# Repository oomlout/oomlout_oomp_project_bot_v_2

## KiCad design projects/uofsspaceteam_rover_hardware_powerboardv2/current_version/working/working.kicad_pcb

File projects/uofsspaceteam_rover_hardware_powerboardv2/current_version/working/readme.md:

# rover_hardware
 
## summary 
* id: uofsspaceteam_rover_hardware_powerboardv2
* user: uofsspaceteam
* name: rover_hardware
* board: powerboardv2
* repo: https://github.com/UofSSpaceTeam/rover-hardware
* src_file_repo_kicad_pcb: Projects/Power Distribution/PowerBoardV2/gerber/PowerBoardV2.kicad_pcb
* src_file_repo_kicad_pcb_link: https://github.com/UofSSpaceTeam/rover-hardware/tree/master/Projects/Power Distribution/PowerBoardV2/gerber/PowerBoardV2.kicad_pcb
* src_file_repo_kicad_sch: Projects/Power Distribution/DriveController/DriveControllerPower.kicad_sch
* src_file_repo_kicad_sch_link: https://github.com/UofSSpaceTeam/rover-hardware/tree/master/Projects/Power Distribution/DriveController/DriveControllerPower.kicad_sch
* src_file_repo_brd: Projects/Communication/KiCad_USB/modified_eagle_files/RH025.1.brd
* src_file_repo_brd_link: https://github.com/UofSSpaceTeam/rover-hardware/tree/master/Projects/Communication/KiCad_USB/modified_eagle_files/RH025.1.brd
* src_file_repo_sch: Projects/Power Distribution/PowerBoardV2/PowerBoardV2.sch
* src_file_repo_sch_link: https://github.com/UofSSpaceTeam/rover-hardware/tree/master/Projects/Power Distribution/PowerBoardV2/PowerBoardV2.sch
* full details link: https://github.com/oomlout/oomlout_oomp_project_bot_v_2/tree/main/projects/uofsspaceteam_rover_hardware_powerboardv2/current_version/working

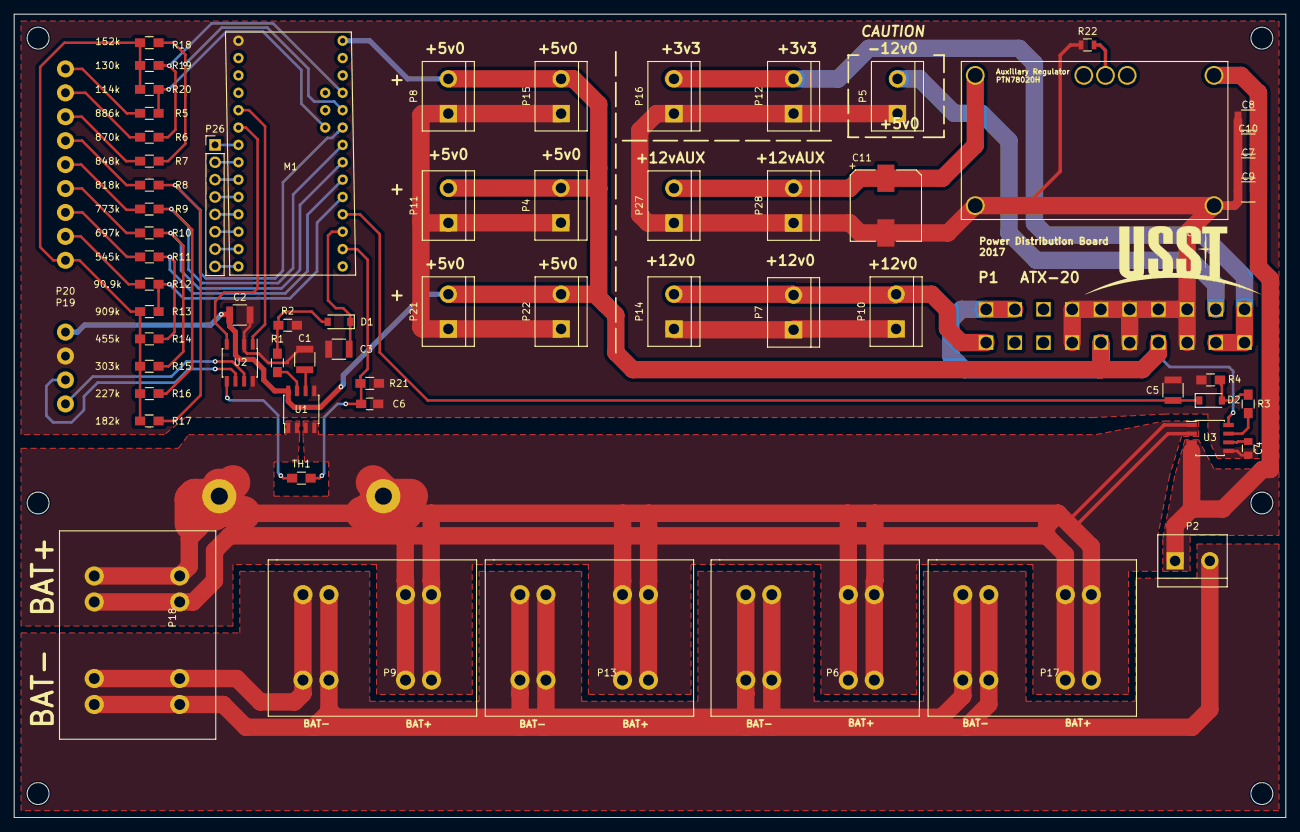
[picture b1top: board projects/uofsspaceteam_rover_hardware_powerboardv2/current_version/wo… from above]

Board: 2 copper layers, 186.0 x 117.5 mm, 65 parts (1 on the bottom side), 49 nets.

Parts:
C1: 1nF; C_1210
C2: 0.1uF; C_1210
C3, C5: Test; C_1210
C4: 1nF; C_0805
C6: 100n; C_0805_HandSoldering
C7, C8, C9, C10: 4.7u; C_1210
C11: 330u; CP_Elec_10x10.5
D1, D2: 1N4448W; D_SOD-123
M1: Teensy3; Teensy_3.2_NoTail
P1: ATX-20; ATX20
P2, P4, P5, P7, P8, P10, P11, P12, P14, P15, P16, P21, P22, P27, P28: CONN_2; Molex_39531_1002
P6, P9, P13, P17, P18: CONN_2; Phoenix_Contact_1770539
P19: CAN_CONN; Molex_39502_1004R
P20: BAT_CONN; Molex_39502_1009R
P26: CONN_8; Socket_Strip_Straight_1x08_Pitch2.54mm
R1, R3: 2k; R_0805_HandSoldering
R2, R4, R21: 10k; R_0805_HandSoldering
R5: 886k; R_0805_HandSoldering
R6: 870k; R_0805_HandSoldering
R7: 848k; R_0805_HandSoldering
R8: 818k; R_0805_HandSoldering
R9: 773k; R_0805_HandSoldering
R10: 697k; R_0805_HandSoldering
R11: 545k; R_0805_HandSoldering
R12: 90.9k; R_0805_HandSoldering
R13: 909k; R_0805_HandSoldering
R14: 455k; R_0805_HandSoldering
R15: 303k; R_0805_HandSoldering
R16: 227k; R_0805_HandSoldering
R17: 182k; R_0805_HandSoldering
R18: 152k; R_0805_HandSoldering
R19: 130k; R_0805_HandSoldering
R20: 114k; R_0805_HandSoldering
R22: 383k; R_0805
TH1: NTC-10k; R_0805_HandSoldering
U1, U3: ACS712; SOIC-8_3.9x4.9mm_Pitch1.27mm
U2: MCP2562; SOIC-8_3.9x4.9mm_Pitch1.27mm
U4: PTN78020; PTN7820H

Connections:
3v3: P1.1, P1.2, P1.3, P12.2, P16.2
5v0: C2.2, M1.VIN, P1.7, P1.11, P1.18, P1.20, P4.2, P8.2, P11.2, P15.2, P19.1, P21.2, P22.2, U1.8, U2.3, U3.8
+12v: P1.19, P7.2, P10.2, P14.2
-12v: P1.4, P5.2
/PowerMonitor/1+: M1.17, R12.1, R13.1
/PowerMonitor/2+: M1.18, R11.1, R14.1
/PowerMonitor/3+: M1.19, R10.1, R15.1
/PowerMonitor/3v3: TH1.1, U2.5
/PowerMonitor/4+: M1.20, R9.1, R16.1
/PowerMonitor/5+: M1.21, R8.1, R17.1
/PowerMonitor/6+: M1.22, R7.1, R18.1
/PowerMonitor/7+: M1.23, R6.1, R19.1
/PowerMonitor/8+: M1.A11, R5.1, R20.1
/PowerMonitor/AUX1: M1.5, P26.1
/PowerMonitor/AUX2: M1.6, P26.2
/PowerMonitor/AUX3: M1.7, P26.3
/PowerMonitor/AUX4: M1.8, P26.4
/PowerMonitor/AUX5: M1.9, P26.5
/PowerMonitor/AUX6: M1.10, P26.6
/PowerMonitor/AUX7: M1.11, P26.7
/PowerMonitor/AUX8: M1.12, P26.8
/PowerMonitor/CANH: P19.4, U2.7
/PowerMonitor/CANL: P19.3, U2.6
/PowerMonitor/I_SENSE1: C3.1, D1.1, M1.15
/PowerMonitor/I_SENSE2: C5.1, D2.1, M1.16
/PowerMonitor/Temp: C6.1, M1.14, R21.1, TH1.2
GND: P2.2, P6.1, P9.1, P13.1, P17.1, P18.1
GND_REG: C1.2, C2.1, C3.2, C4.2, C5.2, C6.2, C7.1, C8.1, C9.1, C10.1, C11.2, M1.GND, P1.5, P1.6, P1.8, P1.9, P1.10, P1.12, P1.13, P1.14, P4.1, P5.1, P7.1, P8.1, P10.1, P11.1, P12.1, P14.1, P15.1, P16.1, P19.2, P21.1, P22.1, P27.1, P28.1, R2.2, R4.2, R21.2, R22.1, U1.5, U2.2, U2.8, U3.5, U4.1, U4.7
unnamed: C1.1, U1.6
unnamed: C4.1, U3.6
unnamed: C11.1, P27.2, P28.2, U4.6
unnamed: D1.2, R1.1, R2.1
unnamed: D2.2, R3.1, R4.1
unnamed: M1.3, U2.1
unnamed: M1.4, U2.4
unnamed: P20.1, R13.2, R14.2, R15.2, R16.2, R17.2, R18.2, R19.2, R20.2
unnamed: P20.2, R12.2
unnamed: P20.3, R11.2
unnamed: P20.4, R10.2
unnamed: P20.5, R9.2
unnamed: P20.6, R8.2
unnamed: P20.7, R7.2
unnamed: P20.8, R6.2
unnamed: P20.9, R5.2
unnamed: R1.2, U1.7
unnamed: R3.2, U3.7
unnamed: R22.2, U4.4
VBAT: P6.2, P9.2, P13.2, P17.2, P18.2, U1.1, U1.2, U1.3, U1.4, U3.1, U3.2
VLOG: C7.2, C8.2, C9.2, C10.2, P2.1, U3.3, U3.4, U4.2

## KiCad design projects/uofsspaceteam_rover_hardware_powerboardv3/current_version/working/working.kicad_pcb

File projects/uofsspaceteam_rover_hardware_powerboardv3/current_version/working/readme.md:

# rover_hardware
 
## summary 
* id: uofsspaceteam_rover_hardware_powerboardv3
* user: uofsspaceteam
* name: rover_hardware
* board: powerboardv3
* repo: https://github.com/UofSSpaceTeam/rover-hardware
* src_file_repo_kicad_pcb: Projects/Power Distribution/PowerBoardV3/PowerBoardV3.kicad_pcb
* src_file_repo_kicad_pcb_link: https://github.com/UofSSpaceTeam/rover-hardware/tree/master/Projects/Power Distribution/PowerBoardV3/PowerBoardV3.kicad_pcb
* src_file_repo_kicad_sch: Projects/Power Distribution/DriveController/DriveControllerPower.kicad_sch
* src_file_repo_kicad_sch_link: https://github.com/UofSSpaceTeam/rover-hardware/tree/master/Projects/Power Distribution/DriveController/DriveControllerPower.kicad_sch
* src_file_repo_brd: Projects/Communication/KiCad_USB/modified_eagle_files/RH025.1.brd
* src_file_repo_brd_link: https://github.com/UofSSpaceTeam/rover-hardware/tree/master/Projects/Communication/KiCad_USB/modified_eagle_files/RH025.1.brd
* src_file_repo_sch: Projects/Power Distribution/PowerBoardV2/PowerBoardV2.sch
* src_file_repo_sch_link: https://github.com/UofSSpaceTeam/rover-hardware/tree/master/Projects/Power Distribution/PowerBoardV2/PowerBoardV2.sch
* full details link: https://github.com/oomlout/oomlout_oomp_project_bot_v_2/tree/main/projects/uofsspaceteam_rover_hardware_powerboardv3/current_version/working

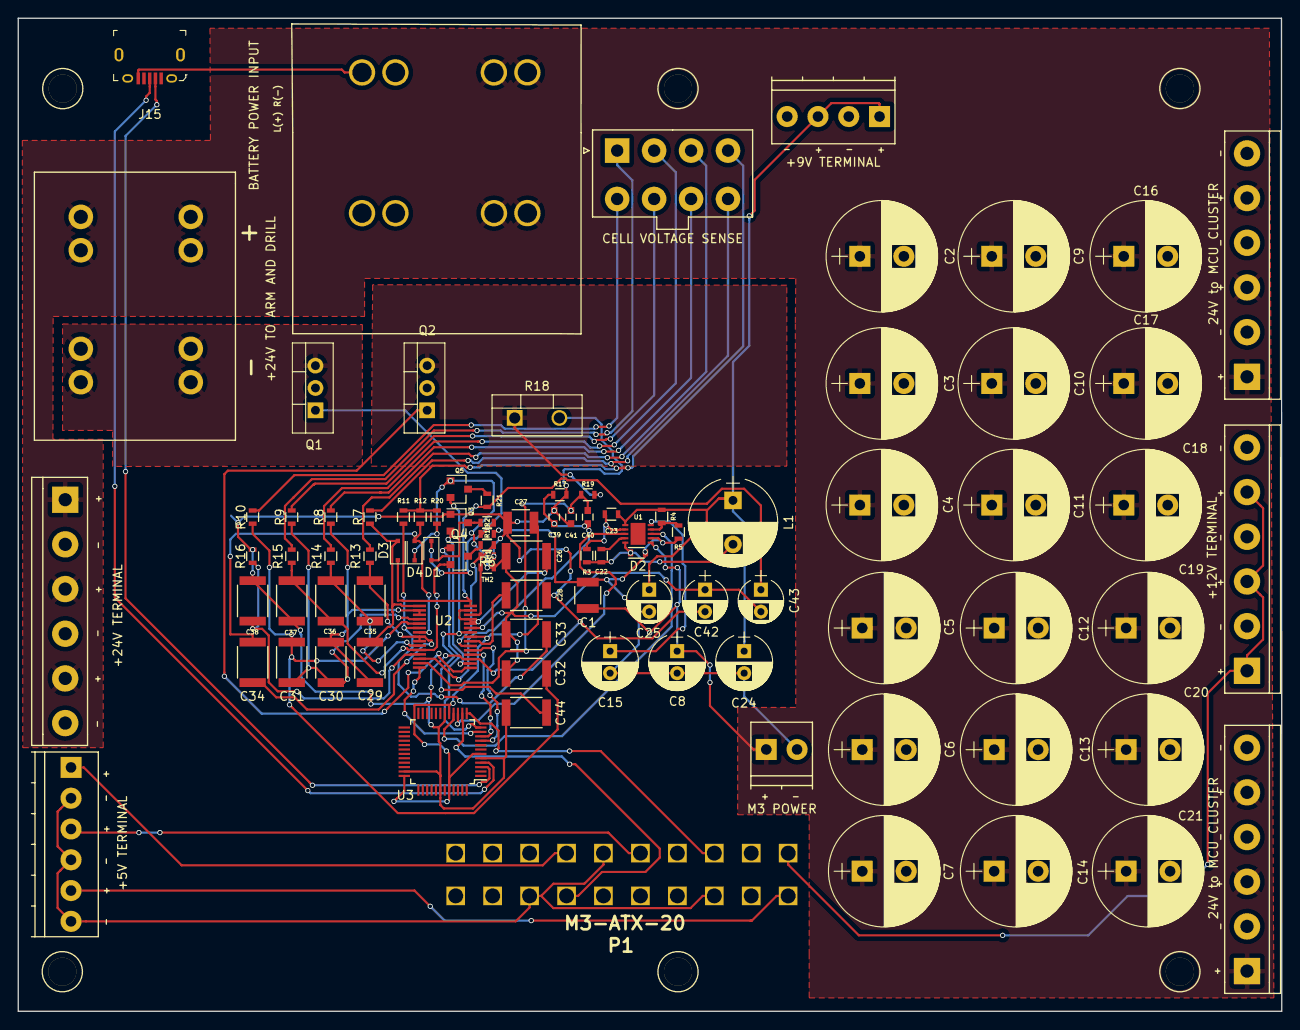
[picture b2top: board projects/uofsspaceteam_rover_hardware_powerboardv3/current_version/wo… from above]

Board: 2 copper layers, 143.7 x 112.9 mm, 92 parts (0 on the bottom side), 60 nets.

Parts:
24V to MCU CLUSTER: MC_STACK_1; TerminalBlock_Pheonix_PT-5mm_6pol
24V to MCU CLUSTER#2: MC_STACK_2; TerminalBlock_Pheonix_PT-5mm_6pol
+5V TERMINAL: 5V_INT_PWR_BLK; TerminalBlock_Phoenix_PT-3.5mm_6pol
+9V TERMINAL: 9V_PWR_TERMBLK; TerminalBlock_Pheonix_PT-3.5mm_4pol
+12V TERMINAL: 12V_INT_PWR_BLK; TerminalBlock_Pheonix_PT-5mm_6pol
+24V TERMINAL: 24V_INT_PWR_BLK; TerminalBlock_Pheonix_PT-5mm_6pol
+24V TO ARM AND DRILL: BACK_EXT_24V; Phoenix_Contact_1770539
BATTERY POWER INPUT: BATT_PWR; Phoenix_Contact_1845344_Ver2
C1: 4.7uF; C_1210
C2, C3, C4, C5, C6, C7, C9, C10, C11, C12, C13, C14, C16, C17, C18, C19, C20, C21: 680uF; CP_Radial_D12.5mm_P5.00mm
C8, C15: 100uF; CP_Radial_D6.3mm_P2.50mm
C22, C23: 10nF; R_0603
C24: 68uF; CP_Radial_D6.3mm_P2.50mm
C25: 10uF; CP_Radial_D5.0mm_P2.50mm
C26, C28, C29, C30, C31, C32, C33, C34, C35, C36, C37, C38, C44: 1 uF; C_1812
C27: 4.7 uF; C_1210
C39, C40, C41: 0.1uF; C_0603
C42, C43: 10 uF; CP_Radial_D5.0mm_P2.50mm
CELL VOLTAGE SENSE: Cell Voltage Sense; Molex_MiniFit-JR-5556-08A_2x04x4.20mm_Straight
D1: D_Small_ALT; D_SOD-323F
D2: D_Zener_Small_ALT; D_0603
D3, D4: D_Small; D_SOD-323F
J15: USB_OTG; USB_Micro_B_Female_10118194-0001LF
L1: 39uH; CP_Radial_D10.0mm_P5.00mm
M3 POWER: M3-ATX-20-PWR; TerminalBlock_Phoenix_PT-3.5mm_2pol
P1: M3-ATX-20; ATX20
Q1, Q2: IRF3205; TO-220-3_Vertical
Q3: BSS84; SOT-23
Q4: BSS83P; SOT-23
Q5: BSS138; SOT-23
R1, R2: 1M; R_0603
R3: 20k; R_0603
R4: 300k; R_0603
R5: 30k; R_0603
R6: 10k; R_0603
R7, R8, R9, R10, R11, R12, R13, R14, R15, R16: 1k; R_0603
R17, R19, R20, R21: 100; R_0603
R18: 5m; TO-220-2_Vertical_Ver2
TH1, TH2: 10k; R_0603
U1: MP2492; QFN_10
U2: bq76930; 30-TSSOP
U3: SAMD21; TQFP-48_7x7mm_Pitch0.5mm

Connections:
+5V_1: +5V TERMINAL.1, P1.7
+5V_2: +5V TERMINAL.3, P1.11
+5V_3: +5V TERMINAL.5, P1.20
+9V: +9V TERMINAL.1, +9V TERMINAL.3, C23.1, C24.1, C25.1, L1.1, R4.1, U1.6
+12V: +12V TERMINAL.1, +12V TERMINAL.3, +12V TERMINAL.5, P1.19
-5V: +5V TERMINAL.2, +5V TERMINAL.4, +5V TERMINAL.6, P1.6, P1.9, P1.16
-12V: 24V to MCU CLUSTER.2, 24V to MCU CLUSTER.4, 24V to MCU CLUSTER.6, 24V to MCU CLUSTER#2.2, 24V to MCU CLUSTER#2.4, 24V to MCU CLUSTER#2.6, +9V TERMINAL.2, +9V TERMINAL.4, +12V TERMINAL.2, +12V TERMINAL.4, +12V TERMINAL.6, +24V TERMINAL.2, +24V TERMINAL.4, +24V TERMINAL.6, +24V TO ARM AND DRILL.2, C1.2, C2.2, C3.2, C4.2, C5.2, C6.2, C7.2, C8.2, C9.2, C10.2, C11.2, C12.2, C13.2, C14.2, C15.2, C16.2, C17.2, C18.2, C19.2, C20.2, C21.2, C24.2, C25.2, D2.2, M3 POWER.2, P1.10, P1.12, P1.14, Q1.3, R1.2, R5.2, U1.2
/HighPowerCircuit/9V_EN: U1.3, U3.16
/HighPowerCircuit/CHG: Q3.2, U2.2
/HighPowerCircuit/CHG_T: Q1.2, Q2.2
/HighPowerCircuit/DSG: Q2.1, U2.1
/HighPowerCircuit/FB: R4.2, R5.1, U1.4
/HighPowerCircuit/PG: P1.15, U3.13
/HighPowerCircuit/SENSE_R: Q2.3, R18.1, R19.1
/Low Power Circuit /9V_PGOOD: U1.8, U3.15
/Low Power Circuit /PG: P1.8, U3.14
A: CELL VOLTAGE SENSE.4, R11.1, R12.1, R20.2
ALERT: U2.30, U3.11
BAT1: C43.1, D3.1, R21.2, U2.15
BATT+: 24V to MCU CLUSTER.1, 24V to MCU CLUSTER.3, 24V to MCU CLUSTER.5, 24V to MCU CLUSTER#2.1, 24V to MCU CLUSTER#2.3, 24V to MCU CLUSTER#2.5, +24V TERMINAL.1, +24V TERMINAL.3, +24V TERMINAL.5, +24V TO ARM AND DRILL.1, BATTERY POWER INPUT.2, C1.1, C2.1, C3.1, C4.1, C5.1, C6.1, C7.1, C8.1, C9.1, C10.1, C11.1, C12.1, C13.1, C14.1, C16.1, C17.1, C18.1, C19.1, C20.1, C21.1, M3 POWER.1, U1.1
BOOT_MC: Q4.1, U3.12
BOOT_TS1: Q4.3, R6.2
BOOT_VC1: C36.1, C37.2, Q4.2, R15.2, U2.26
CAP2: C26.1, C32.1, C33.2, C42.1, C43.2, D4.1, Q5.1, R20.1, TH2.2, U2.10
CELL_1+: CELL VOLTAGE SENSE.1, R15.1
CELL_2+: CELL VOLTAGE SENSE.2, R14.1
CELL_3+: CELL VOLTAGE SENSE.3, R13.1
CELL_5+: CELL VOLTAGE SENSE.5, R10.1
CELL_6+: CELL VOLTAGE SENSE.6, R9.1
CELL_7+: CELL VOLTAGE SENSE.7, R8.1
CELL_8+: CELL VOLTAGE SENSE.8, R7.1
Cell_1-: BATTERY POWER INPUT.1, C27.2, C28.1, C37.1, C38.2, C39.1, C41.2, C42.2, C44.2, J15.5, Q3.1, R16.1, R17.1, R18.2, TH1.2, U2.3, U3.5, U3.18, U3.35, U3.42
unnamed: C15.1, U1.5
unnamed: C22.1, D2.1, L1.2, R3.2, U1.10
unnamed: C22.2, U1.9
unnamed: C23.2, R3.1, U1.7
unnamed: C26.2, U2.11, U2.12, U2.14
unnamed: C28.2, U2.7
unnamed: C29.1, C30.2, R8.2, U2.17, U2.18
unnamed: C29.2, D3.2, R7.2, U2.16
unnamed: C30.1, C31.2, R9.2, U2.19
unnamed: C31.1, C32.2, R10.2, U2.20
unnamed: C33.1, R11.2, U2.21
unnamed: C34.1, C35.2, R13.2, U2.23, U2.24
unnamed: C34.2, D4.2, R12.2, U2.22
unnamed: C35.1, C36.2, R14.2, U2.25
unnamed: C38.1, R16.2, U2.27
unnamed: D1.1, Q1.1, R1.1, R2.2
unnamed: D1.2, Q3.3, R2.1
unnamed: Q5.3, R21.1
unnamed: R6.1, TH1.1, U2.6
unnamed: TH2.1, U2.13
REGSRC: C44.1, Q5.2, U2.9
SCL: U2.5, U3.9
SDA: U2.4, U3.10
SRN: C40.2, C41.1, R19.2, U2.29
SRP: C39.2, C40.1, R17.2, U2.28
USB_D+: J15.3, U3.4
USB_D-: J15.2, U3.3
VCC: C27.1, U2.8, U3.6, U3.17, U3.36, U3.44

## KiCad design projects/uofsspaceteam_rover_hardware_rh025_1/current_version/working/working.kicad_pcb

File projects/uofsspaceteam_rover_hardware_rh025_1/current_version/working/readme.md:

# rover_hardware
 
## summary 
* id: uofsspaceteam_rover_hardware_rh025_1
* user: uofsspaceteam
* name: rover_hardware
* board: rh025_1
* repo: https://github.com/UofSSpaceTeam/rover-hardware
* src_file_repo_kicad_pcb: Projects/Communication/KiCad_USB/RH025.1.kicad_pcb
* src_file_repo_kicad_pcb_link: https://github.com/UofSSpaceTeam/rover-hardware/tree/master/Projects/Communication/KiCad_USB/RH025.1.kicad_pcb
* src_file_repo_kicad_sch: Projects/Communication/CANBoard/CANBus.kicad_sch
* src_file_repo_kicad_sch_link: https://github.com/UofSSpaceTeam/rover-hardware/tree/master/Projects/Communication/CANBoard/CANBus.kicad_sch
* src_file_repo_brd: Projects/Communication/KiCad_USB/modified_eagle_files/RH025.1.brd
* src_file_repo_brd_link: https://github.com/UofSSpaceTeam/rover-hardware/tree/master/Projects/Communication/KiCad_USB/modified_eagle_files/RH025.1.brd
* src_file_repo_sch: Projects/Communication/KiCad_USB/RH025.1.sch
* src_file_repo_sch_link: https://github.com/UofSSpaceTeam/rover-hardware/tree/master/Projects/Communication/KiCad_USB/RH025.1.sch
* full details link: https://github.com/oomlout/oomlout_oomp_project_bot_v_2/tree/main/projects/uofsspaceteam_rover_hardware_rh025_1/current_version/working

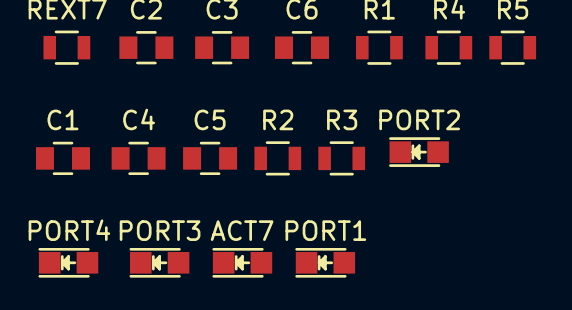
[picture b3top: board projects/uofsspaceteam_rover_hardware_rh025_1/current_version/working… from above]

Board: 2 copper layers, 17 parts (0 on the bottom side), 5 nets, no tracks yet.

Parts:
ACT7: LED_0805
C1, C3, C6: 0.1uF; C_0805
C2, C4, C5: 10uF; C_0805
PORT1, PORT2, PORT3, PORT4: LED_0805
R1: 100K; R_0805
R2: 47K; R_0805
R3, R4, R5: 330; R_0805
REXT7: 2.7K; R_0805

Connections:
3V3: C1.1, C2.1
/N$8: C3.1, C4.1
/N$13: R1.2, R2.1
GND: C1.2, C2.2, C3.2, C4.2, C5.2, C6.2, R1.1, R5.1, REXT7.1
VBUS: C5.1, C6.1, R2.2

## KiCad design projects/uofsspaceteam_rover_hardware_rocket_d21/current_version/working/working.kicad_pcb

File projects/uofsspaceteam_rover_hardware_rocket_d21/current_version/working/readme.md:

# rover_hardware
 
## summary 
* id: uofsspaceteam_rover_hardware_rocket_d21
* user: uofsspaceteam
* name: rover_hardware
* board: rocket_d21
* repo: https://github.com/UofSSpaceTeam/rover-hardware
* src_file_repo_kicad_pcb: Projects/Computer Boards/rocket_board/designs/designs/rocket-d21-min/rocket-d21.kicad_pcb
* src_file_repo_kicad_pcb_link: https://github.com/UofSSpaceTeam/rover-hardware/tree/master/Projects/Computer Boards/rocket_board/designs/designs/rocket-d21-min/rocket-d21.kicad_pcb
* src_file_repo_kicad_sch: Projects/Computer Boards/PiMainboard/CameraModule.kicad_sch
* src_file_repo_kicad_sch_link: https://github.com/UofSSpaceTeam/rover-hardware/tree/master/Projects/Computer Boards/PiMainboard/CameraModule.kicad_sch
* src_file_repo_brd: Projects/Communication/KiCad_USB/modified_eagle_files/RH025.1.brd
* src_file_repo_brd_link: https://github.com/UofSSpaceTeam/rover-hardware/tree/master/Projects/Communication/KiCad_USB/modified_eagle_files/RH025.1.brd
* src_file_repo_sch: Projects/Computer Boards/rocket_board/designs/designs/rocket-d21-min/rocket-d21.sch
* src_file_repo_sch_link: https://github.com/UofSSpaceTeam/rover-hardware/tree/master/Projects/Computer Boards/rocket_board/designs/designs/rocket-d21-min/rocket-d21.sch
* full details link: https://github.com/oomlout/oomlout_oomp_project_bot_v_2/tree/main/projects/uofsspaceteam_rover_hardware_rocket_d21/current_version/working

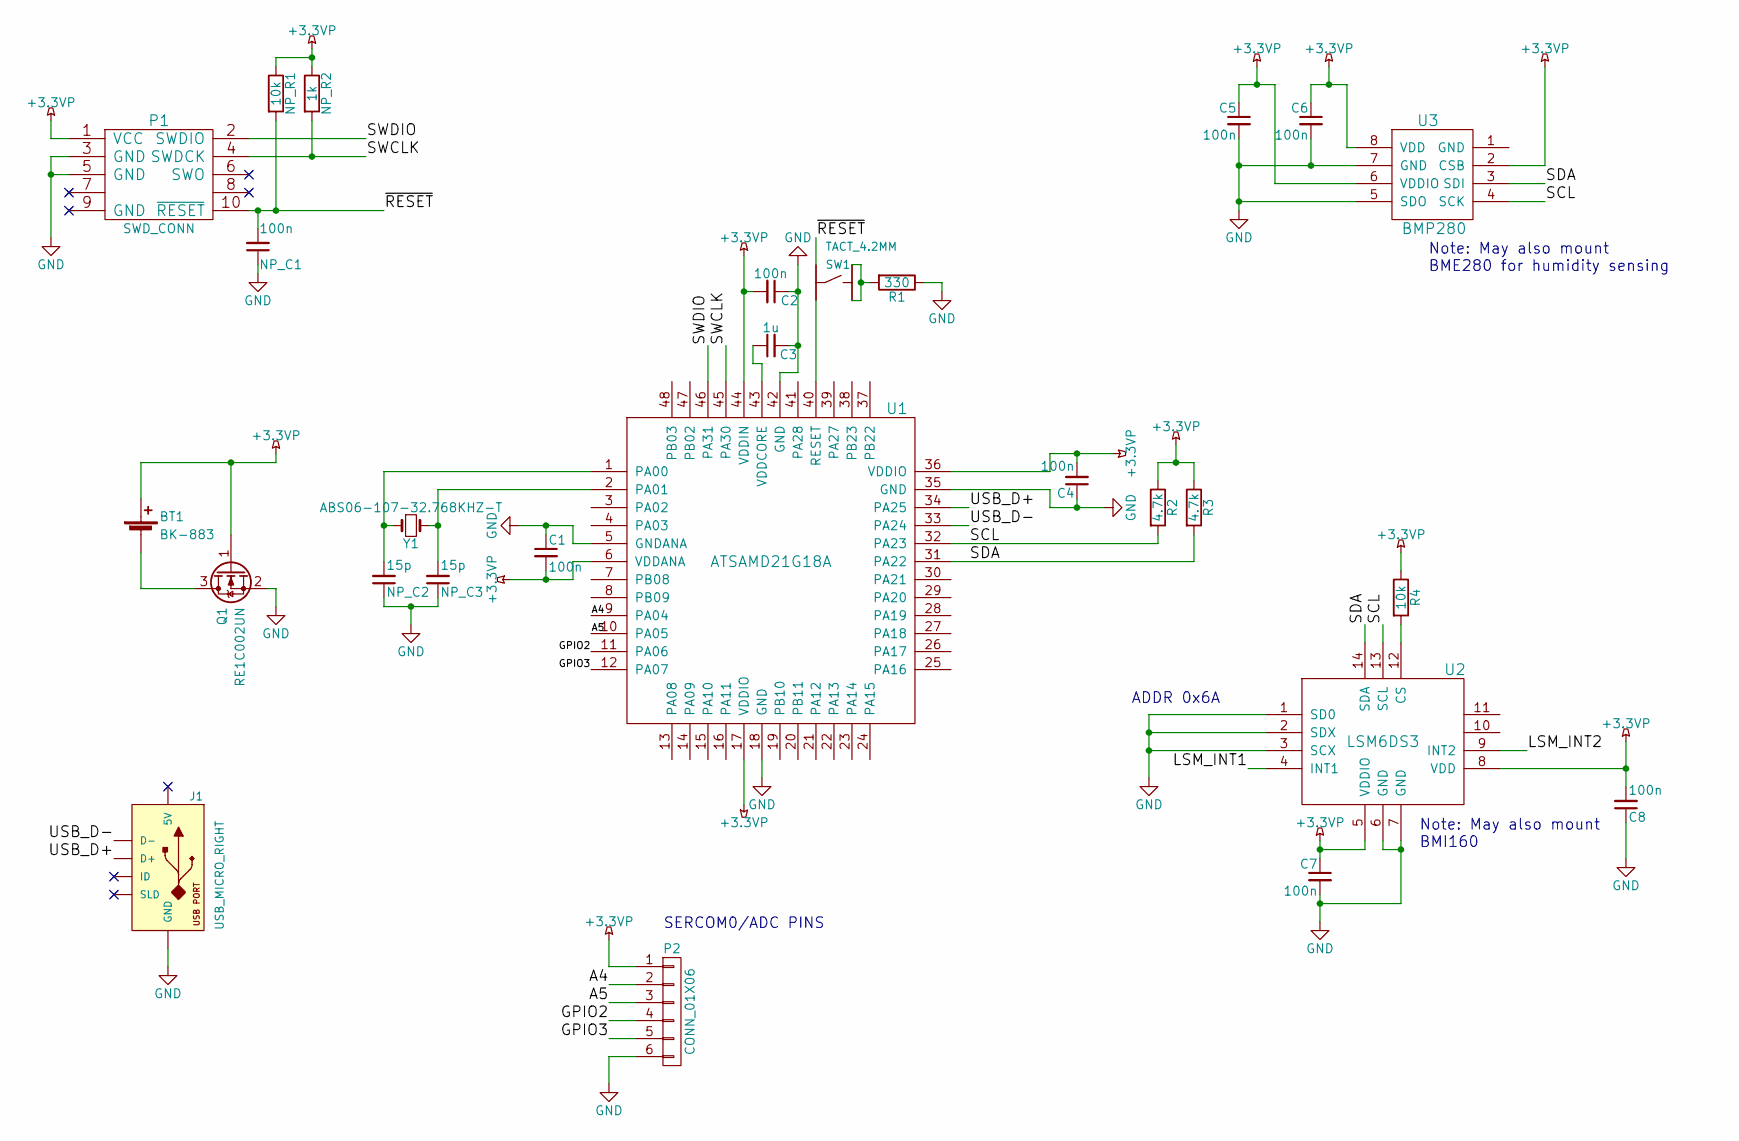
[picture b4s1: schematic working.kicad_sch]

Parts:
BT1: BK-883; BK-833
C1, C2, C4, C5, C6, C7, C8: 100n; C_0603
C3: 1u; C_0603
J1: USB_MICRO_RIGHT; MF_Connectors-MICROUSB-RIGHT
NP_C1: 100n; C_0603
NP_C2, NP_C3: 15p; C_0603
NP_R1: 10k; R_0603
NP_R2: 1k; R_0603
P1: SWD_CONN; Pin_Header_Straight_2x05_Pitch1.27mm
P2: CONN_01X06; Pin_Header_Straight_1x06_Pitch2.54mm
Q1: RE1C002UN; SOT-490
R1: 330; R_0603
R2, R3: 4.7k; R_0603
R4: 10k; R_0603
SW1: TACT_4.2MM; MF_Switches-TACT4.2MM
U1: ATSAMD21G18A; TQFP-48_7x7mm_Pitch0.5mm
U2: LSM6DS3; LGA-14
U3: BMP280; LGA-8
Y1: ABS06-107-32.768KHZ-T; Crystal_SMD_MicroCrystal_CC8V-T1A-2pin_2.0x1.2mm

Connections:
+3.3VP: BT1.1 (+), C1.2, C2.2, C4.2, C5.1, C6.1, C7.1, C8.2, NP_R1.1, NP_R2.1, P1.1 (VCC), P2.1, Q1.1 (G), R2.1, R3.1, R4.1, U1.6 (VDDANA), U1.17 (VDDIO), U1.36 (VDDIO), U1.44 (VDDIN), U2.5 (VDDIO), U2.8 (VDD), U3.2 (CSB), U3.6 (VDDIO), U3.8 (VDD)
/A4: P2.2, U1.9 (PA04)
/A5: P2.3, U1.10 (PA05)
/GPIO2: P2.4, U1.11 (PA06)
/GPIO3: P2.5, U1.12 (PA07)
/LSM_INT1: U2.4 (INT1)
/LSM_INT2: U2.9 (INT2)
/SCL: R2.2, U1.32 (PA23), U2.13 (SCL), U3.4 (SCK)
/SDA: R3.2, U1.31 (PA22), U2.14 (SDA), U3.3 (SDI)
/SWCLK: NP_R2.2, P1.4 (SWDCK), U1.45 (PA30)
/SWDIO: P1.2 (SWDIO), U1.46 (PA31)
/USB_D+: J1.3 (D+), U1.34 (PA25)
/USB_D-: J1.2 (D-), U1.33 (PA24)
/~RESET: NP_C1.2, NP_R1.2, P1.10 (~RESET), SW1.3
GND: C1.1, C2.1, C3.2, C4.1, C5.2, C6.2, C7.2, C8.1, J1.5 (GND), NP_C1.1, NP_C2.1, NP_C3.1, P1.3 (GND), P1.5 (GND), P2.6, Q1.2 (S), R1.1, U1.5 (GNDANA), U1.18 (GND), U1.35 (GND), U1.42 (GND), U2.1 (SD0), U2.2 (SDX), U2.3 (SCX), U2.6 (GND), U2.7 (GND), U3.5 (SDO), U3.7 (GND)
unnamed: BT1.2 (-), Q1.3 (D)
unnamed: C3.1, U1.43 (VDDCORE)
unnamed: NP_C2.2, U1.1 (PA00), Y1.1
unnamed: NP_C3.2, U1.2 (PA01), Y1.2
unnamed: R1.2, SW1.1, SW1.2
unnamed: R4.2, U2.12 (CS)
unnamed: SW1.4, U1.40 (RESET)
SLD: J1.S1 (SLD), J1.S2 (SLD), J1.S3 (SLD), J1.S4 (SLD), J1.S5 (SLD), J1.S6 (SLD)

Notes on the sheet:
Note: May also mount BMI160
ADDR 0x6A
SERCOM0/ADC PINS
Note: May also mount BME280 for humidity sensing

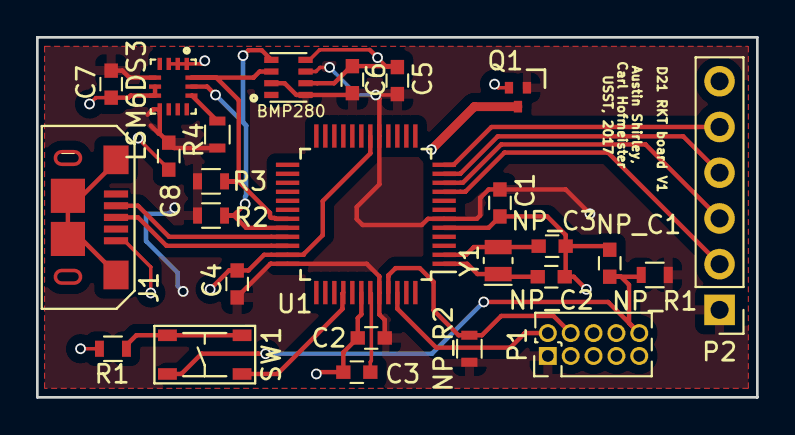
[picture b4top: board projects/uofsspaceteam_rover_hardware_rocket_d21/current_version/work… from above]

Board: 2 copper layers, 40.0 x 20.0 mm, 27 parts (1 on the bottom side), 21 nets.

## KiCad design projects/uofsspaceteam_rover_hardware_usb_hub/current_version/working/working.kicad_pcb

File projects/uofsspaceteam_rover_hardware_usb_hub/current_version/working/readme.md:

# rover_hardware
 
## summary 
* id: uofsspaceteam_rover_hardware_usb_hub
* user: uofsspaceteam
* name: rover_hardware
* board: usb_hub
* repo: https://github.com/UofSSpaceTeam/rover-hardware
* src_file_repo_kicad_pcb: Projects/Power Distribution/TUSB2077A_test_hub/usb_hub.kicad_pcb
* src_file_repo_kicad_pcb_link: https://github.com/UofSSpaceTeam/rover-hardware/tree/master/Projects/Power Distribution/TUSB2077A_test_hub/usb_hub.kicad_pcb
* src_file_repo_kicad_sch: Projects/Power Distribution/DriveController/DriveControllerPower.kicad_sch
* src_file_repo_kicad_sch_link: https://github.com/UofSSpaceTeam/rover-hardware/tree/master/Projects/Power Distribution/DriveController/DriveControllerPower.kicad_sch
* src_file_repo_brd: Projects/Communication/KiCad_USB/modified_eagle_files/RH025.1.brd
* src_file_repo_brd_link: https://github.com/UofSSpaceTeam/rover-hardware/tree/master/Projects/Communication/KiCad_USB/modified_eagle_files/RH025.1.brd
* src_file_repo_sch: Projects/Power Distribution/TUSB2077A_test_hub/usb_hub.sch
* src_file_repo_sch_link: https://github.com/UofSSpaceTeam/rover-hardware/tree/master/Projects/Power Distribution/TUSB2077A_test_hub/usb_hub.sch
* full details link: https://github.com/oomlout/oomlout_oomp_project_bot_v_2/tree/main/projects/uofsspaceteam_rover_hardware_usb_hub/current_version/working

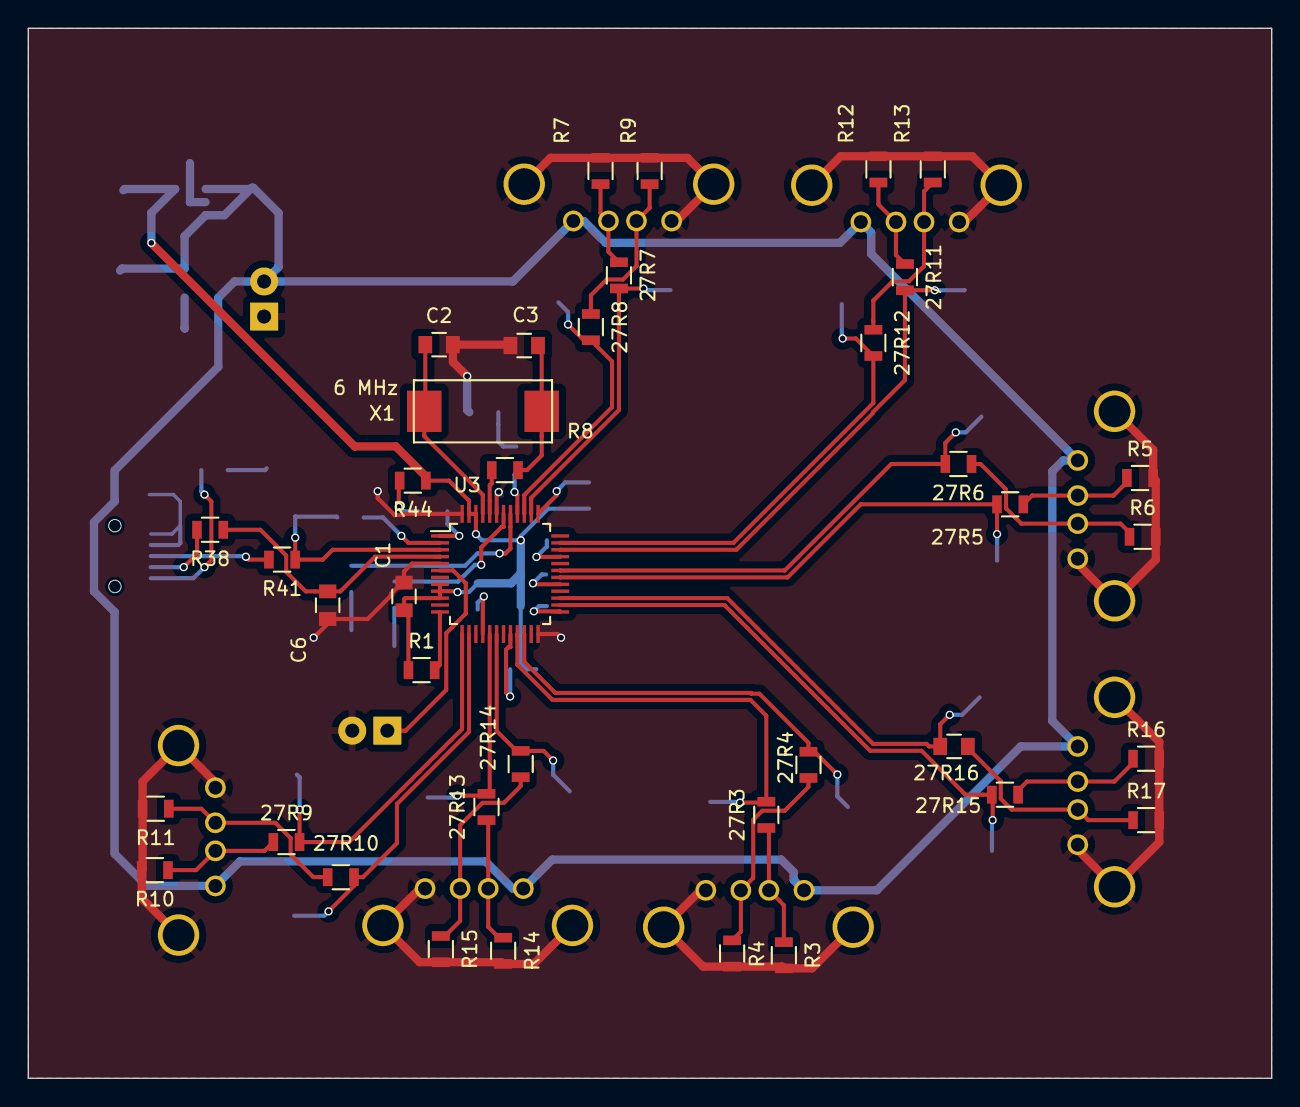
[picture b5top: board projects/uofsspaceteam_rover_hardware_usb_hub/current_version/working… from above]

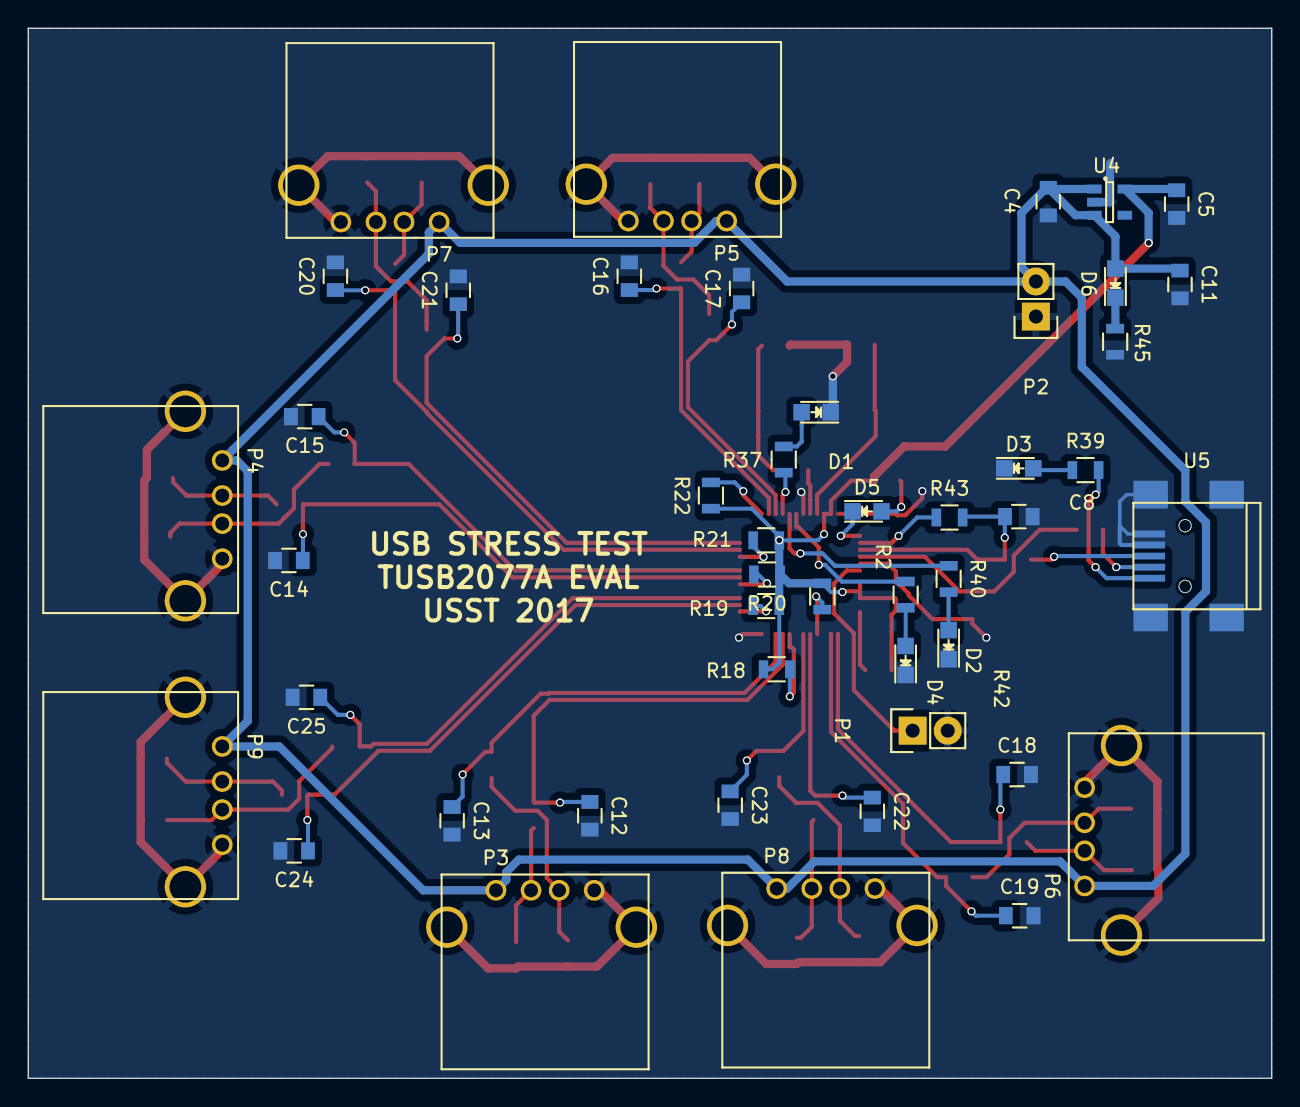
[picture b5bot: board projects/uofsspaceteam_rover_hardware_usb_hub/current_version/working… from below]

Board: 2 copper layers, 90.0 x 76.0 mm, 86 parts (47 on the bottom side), 58 nets.

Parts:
27R3, 27R4, 27R5, 27R6, 27R7, 27R8, 27R9, 27R10, 27R11, 27R12, 27R13, 27R14, 27R15: 27R; R_0805
27R16: 27R; C_0805
C1: 0.1uF; C_0805
C2, C3: 33pF; C_0805
C4: 1uF; C_0805
C5, C11: 10uF; C_0805
C6, C8, C12, C13, C14, C15, C16, C17, C18, C19, C20, C21, C22, C23, C24, C25: 22pF; C_0805
D1, D2, D3, D4, D5, D6: LED; LED_0805
P1: CONN_01X02; Pin_Header_Straight_1x02
P2: CONN_2; Pin_Header_Straight_1x02
P3, P4, P5, P6, P7, P8, P9: USB_A
R1, R2, R3, R4, R5, R6, R7, R9, R10, R11, R12, R13, R14, R15, R16, R17, R18, R19, R20, R21, R22: 15k; R_0805
R8, R43: 1.5k; R_0805
R37, R39, R40, R42, R44, R45: 1k; R_0805
R38, R41: 30; R_0805
U3: TUSB2077A; TQFP-48_7x7mm_Pitch0.5mm
U4: TPS76333; SOT-23-5
U5: USB_A_MALE; USB_Mini-B
X1: 6 MHz; FOX6MHZ

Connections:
+3.3V: C1.1, C5.1, R1.1, R2.1, R18.1, R19.1, R20.1, R21.1, R22.1, R44.1, U3.8, U3.9, U3.10, U3.46, U3.47, U4.5
D0_N: C6.1, R38.1, U3.4
D0_P: C8.1, R41.1, R43.2, U3.3
D1_N: 27R9.2, C18.1, U3.13
D1_P: 27R10.2, C19.1, U3.14
D2_N: 27R13.2, C22.1, U3.17
D2_P: 27R14.2, C23.1, U3.18
D3_N: 27R3.2, C12.1, U3.21
D3_P: 27R4.2, C13.1, U3.22
D4_N: 27R15.2, C24.1, U3.26
D4_P: 27R16.2, C25.1, U3.27
D5_N: 27R5.2, C14.1, U3.30
D5_P: 27R6.2, C15.1, U3.31
D6_N: 27R11.2, C20.1, U3.34
D6_P: 27R12.2, C21.1, U3.35
D7_N: 27R7.2, C16.1, U3.38
D7_P: 27R8.2, C17.1, U3.39
DP0PUR: R43.1, U3.2
GND: C1.2, C2.2, C3.2, C4.2, C5.2, C6.2, C8.2, C11.2, C12.2, C13.2, C14.2, C15.2, C16.2, C17.2, C18.2, C19.2, C20.2, C21.2, C22.2, C23.2, C24.2, C25.2, D1.1, D2.1, D3.1, D4.1, P1.2, P2.1, P3.4, P3.5, P4.4, P4.5, P5.4, P5.5, P6.4, P6.5, P7.4, P7.5, P8.4, P8.5, P9.4, P9.5, R3.2, R4.2, R5.2, R6.2, R7.2, R9.2, R10.2, R11.2, R12.2, R13.2, R14.2, R15.2, R16.2, R17.2, R45.1, U3.5, U3.24, U3.43, U3.48, U4.2, U5.4, U5.5, U5.6
HUBCFG: R37.1, U3.40
unnamed: 27R3.1, P3.2, R3.1
unnamed: 27R4.1, P3.3, R4.1
unnamed: 27R5.1, P4.2, R5.1
unnamed: 27R6.1, P4.3, R6.1
unnamed: 27R7.1, P5.2, R7.1
unnamed: 27R8.1, P5.3, R9.1
unnamed: 27R9.1, P6.2, R10.1
unnamed: 27R10.1, P6.3, R11.1
unnamed: 27R11.1, P7.2, R12.1
unnamed: 27R12.1, P7.3, R13.1
unnamed: 27R13.1, P8.2, R14.1
unnamed: 27R14.1, P8.3, R15.1
unnamed: 27R15.1, P9.2, R16.1
unnamed: 27R16.1, P9.3, R17.1
unnamed: C2.1, U3.45, X1.2
unnamed: C3.1, R8.2, X1.1
unnamed: D1.2, R37.2
unnamed: D2.2, R40.2
unnamed: D3.2, R39.1
unnamed: D4.2, R42.2
unnamed: D5.2, R44.2
unnamed: D6.1, R45.2
unnamed: R1.2, U3.12
unnamed: R2.2, U3.16
unnamed: R8.1, U3.44
unnamed: R18.2, U3.20
unnamed: R19.2, U3.25
unnamed: R20.2, U3.29
unnamed: R21.2, U3.33
unnamed: R22.2, U3.37
unnamed: R38.2, U5.2
unnamed: R39.2, U5.1
unnamed: R41.2, U5.3
PORTDIS: R42.1, U3.42
PORTPWR: R40.1, U3.41
RST: P1.1, U3.6
SPND: D5.1, U3.1
VCC: C4.1, C11.1, D6.2, P2.2, P3.1, P4.1, P5.1, P6.1, P7.1, P8.1, P9.1, U4.1, U4.3
